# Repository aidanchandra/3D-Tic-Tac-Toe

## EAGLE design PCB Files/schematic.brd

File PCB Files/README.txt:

Each PCB is essentially a game piece. Each PCB contains a button, two LEDs (Blue
for player 1, Orange for player 2), and an Attiny85. Each gamepice communicates
with an Arduino UNO through i2c and the Arduino UNO relays that information to
the computer over serial. Information relayed includes which gamepieces have
buttons pressed. The computer also sends commands to the Arduino, which in
turn sends i2c commands to the correct gamepiece in order to perform actions such
as light up a certian color LED to indicate the AI's move.

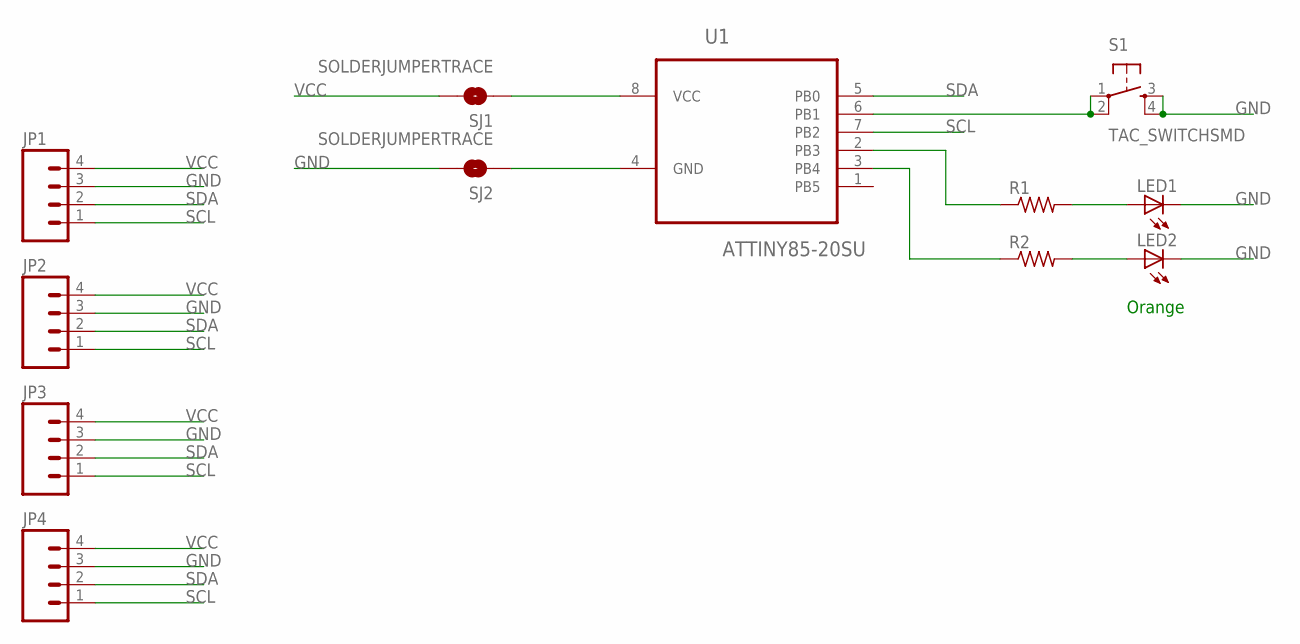
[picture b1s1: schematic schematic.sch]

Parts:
JP1, JP2, JP3, JP4: M041X04_NO_SILK; 1X04_NO_SILK
LED1, LED2: LEDCHIP-LED0805; CHIP-LED0805
R1, R2: R-US_R0805; R0805
S1: TAC_SWITCHSMD; TACTILE-SWITCH-SMD
SJ1, SJ2: SOLDERJUMPERTRACE; SJ_2S-TRACE
U1: ATTINY85-20SU; SOIC127P798X216-8N

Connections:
GND: JP1.3, JP2.3, JP3.3, JP4.3, LED1.C, LED2.C, S1.3, S1.4, SJ2.2
unnamed: R2.1, U1.3 (PB4)
unnamed: R1.1, U1.2 (PB3)
unnamed: LED1.A, R1.2
unnamed: LED2.A, R2.2
unnamed: S1.1, S1.2, U1.6 (PB1)
unnamed: SJ1.1, U1.8 (VCC)
unnamed: SJ2.1, U1.4 (GND)
SCL: JP1.1, JP2.1, JP3.1, JP4.1, U1.7 (PB2)
SDA: JP1.2, JP2.2, JP3.2, JP4.2, U1.5 (PB0)
VCC: JP1.4, JP2.4, JP3.4, JP4.4, SJ1.2

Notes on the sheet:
Orange

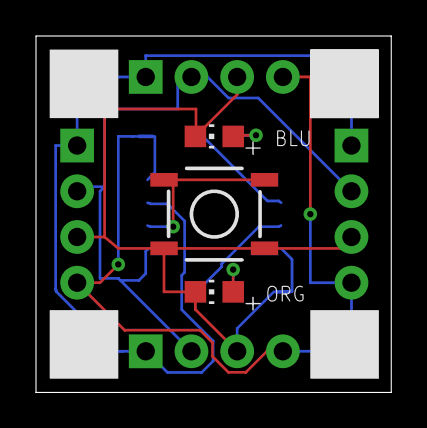
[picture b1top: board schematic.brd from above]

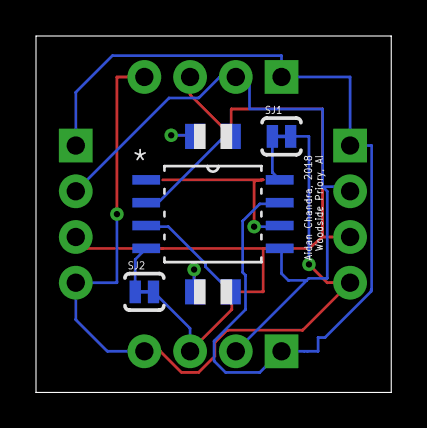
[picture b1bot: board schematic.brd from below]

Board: 2 copper layers, 19.7 x 19.8 mm, 12 parts (5 on the bottom side), 11 nets.

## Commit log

2020-01-13 Added files

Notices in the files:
parts and their libraries:
SparkFun-Connectors: Licensing: Creative Commons ShareAlike 4.0 International - https://creativecommons.org/licenses/by-sa/4.0
